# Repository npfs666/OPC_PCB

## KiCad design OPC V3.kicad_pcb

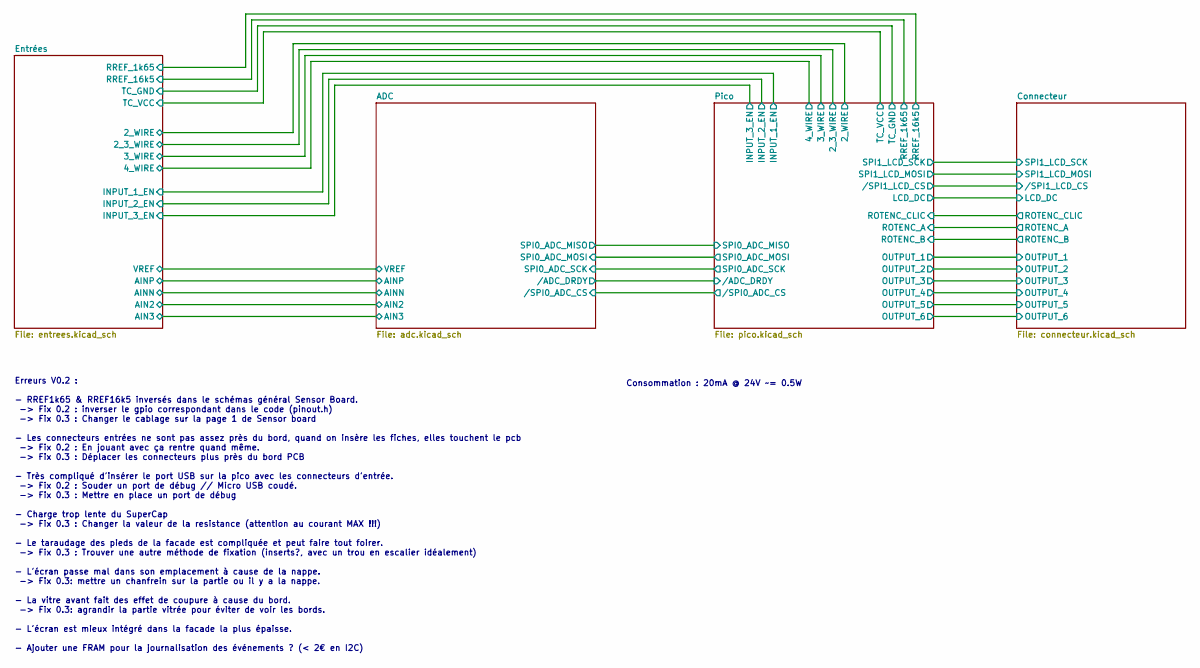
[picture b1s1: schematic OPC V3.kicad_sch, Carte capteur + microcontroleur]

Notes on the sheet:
Erreurs V0.2 : - RREF1k65 & RREF16k5 inversés dans le schémas général Sensor Board. -> Fix 0.2 : inverser le gpio correspondant dans le code (pinout.h) -> Fix 0.3 : Changer le cablage sur la page 1 de Sensor board - Les connecteurs entrées ne sont pas assez près du bord, quand on insère les fiches,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
Consommation : 20mA @ 24V ~= 0.5W

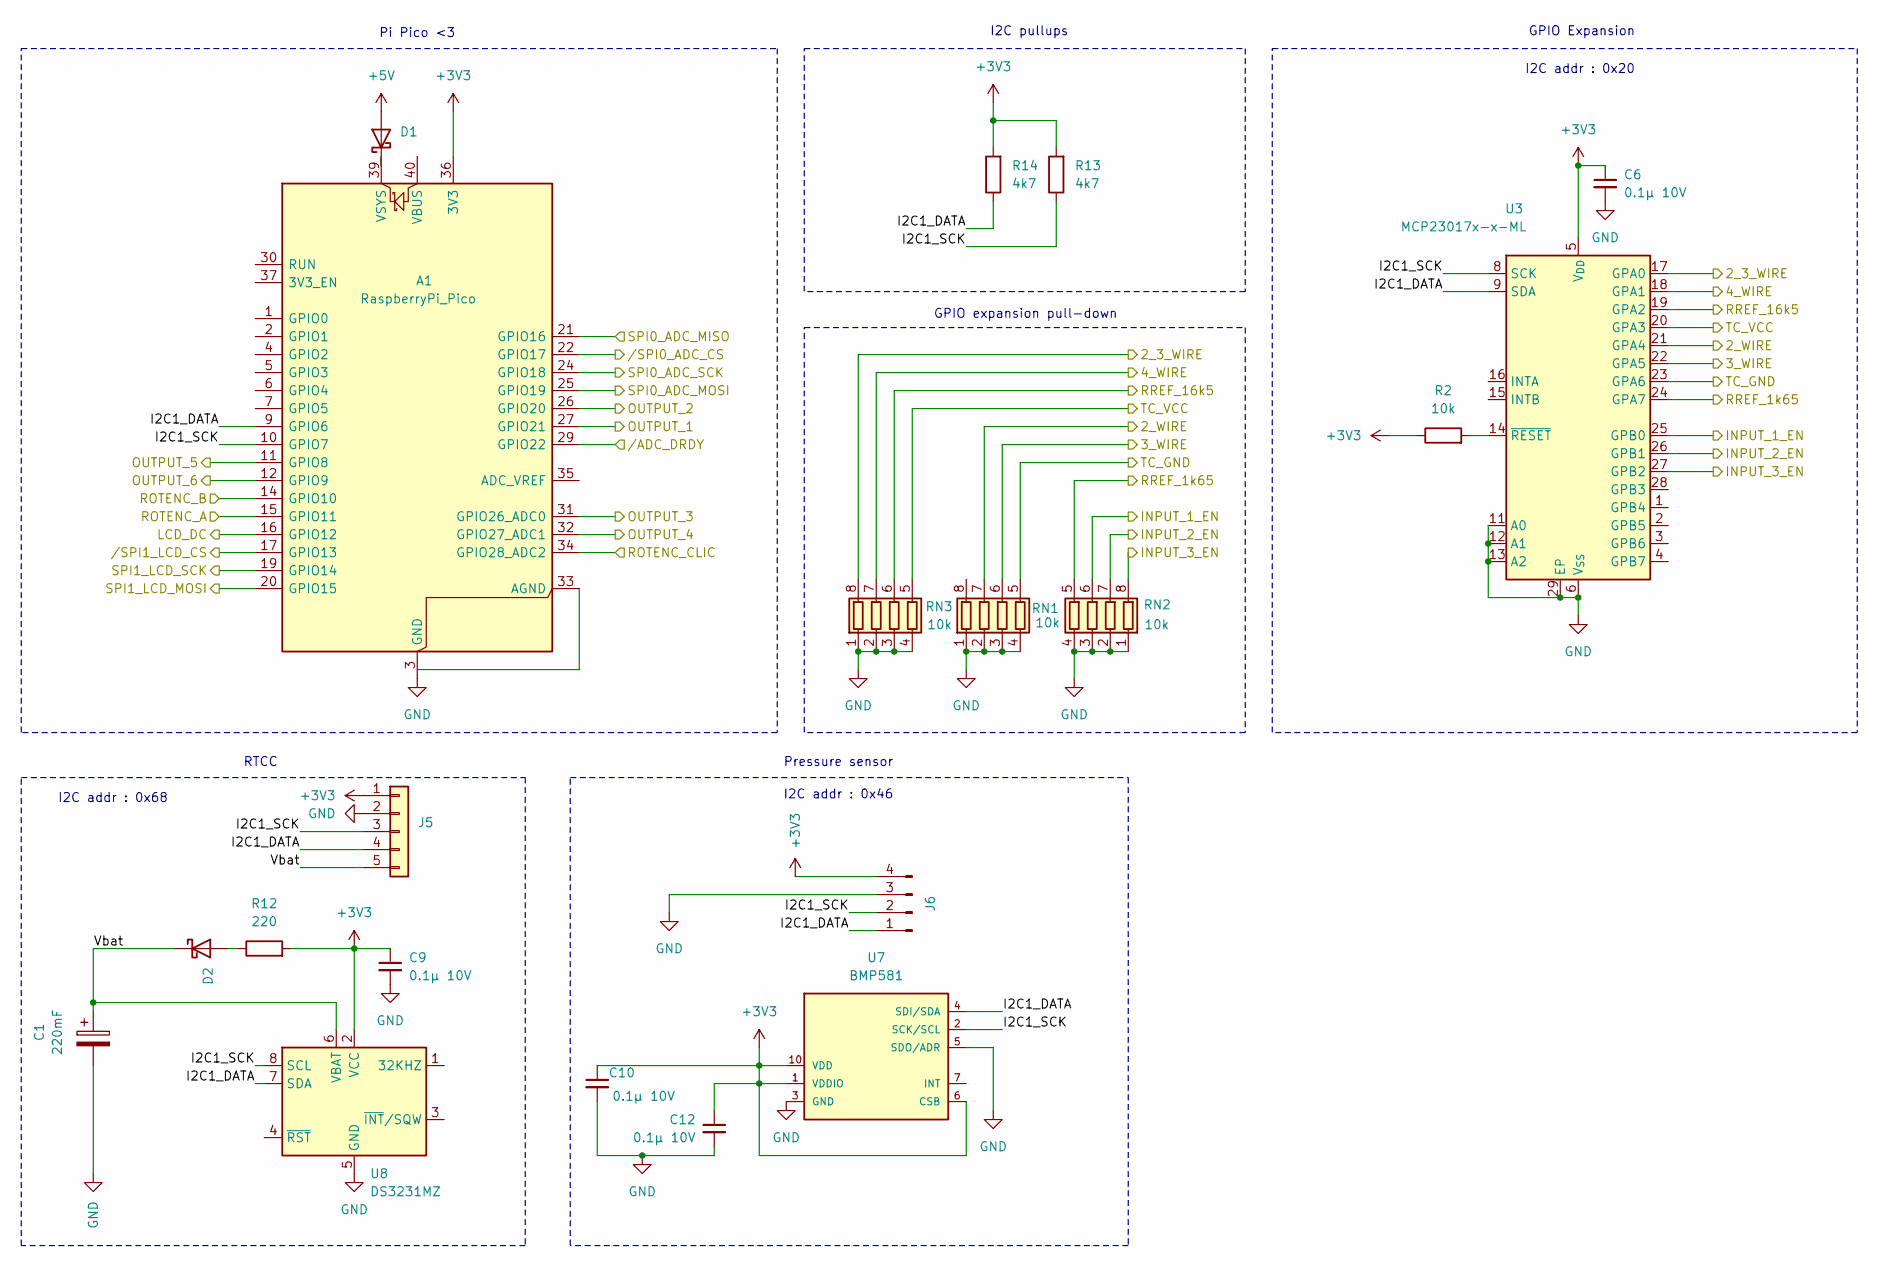
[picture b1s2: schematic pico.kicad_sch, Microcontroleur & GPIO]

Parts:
A1: RaspberryPi_Pico; RaspberryPi_Pico_Common_THT_SIMPLE; MPN SC1631
C1: 220mF; CP_Radial_D13.0mm_P5.00mm; MPN 3-158-695
C6, C9, C12: 0.1µ 10V; C_0603_1608Metric_Pad1.08x0.95mm_HandSolder; MPN 885012206020; LCSC Part # C14663
C10: 0.1µ 10V; C_0603_1608Metric; MPN 885012206020; LCSC Part # C14663
D1, D2: D_Schottky; D_SMA; MPN B140-E3/61T; LCSC Part # C14996
J5: Conn_01x05; PinHeader_1x05_P2.54mm_Vertical
J6: Conn_01x04_Pin; PinHeader_1x04_P2.54mm_Vertical
R2: 10k; R_0603_1608Metric_Pad0.98x0.95mm_HandSolder; MPN ERJ-3EKF1002V; LCSC Part # C25804
R12: 220; R_0603_1608Metric_Pad0.98x0.95mm_HandSolder; MPN ERJ-3GEYJ221V; LCSC Part # C22962
R13, R14: 4k7; R_0603_1608Metric_Pad0.98x0.95mm_HandSolder; MPN ERJ-3GEYJ472V; LCSC Part # C23162
RN1, RN2, RN3: 10k; R_Array_Concave_4x0603; MPN WA06X103JTL; LCSC Part # C29718
U3: MCP23017x-x-ML; QFN-28-1EP_6x6mm_P0.65mm_EP4.25x4.25mm; MPN MCP23017-E/ML; LCSC Part # C629439
U7: BMP581; MPN BMP581
U8: DS3231MZ; SOIC-8_3.9x4.9mm_P1.27mm; MPN DS3231MZ+TRL; LCSC Part # C107410

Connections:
+3V3: A1.36 (3V3), C6.1, C9.1, C10.1, C12.1, J5.1, J6.4, R2.1, R12.2, R13.2, R14.2, U3.5 (V_{DD}), U7.1 (VDDIO), U7.6 (CSB), U7.10 (VDD), U8.2 (VCC); also elsewhere on the board
+5V: D1.2 (A); also elsewhere on the board
/ADC/SPI0_ADC_MISO: A1.21 (GPIO16); also elsewhere on the board
/ADC/SPI0_ADC_MOSI: A1.25 (GPIO19); also elsewhere on the board
/ADC/SPI0_ADC_SCK: A1.24 (GPIO18); also elsewhere on the board
/ADC//ADC_DRDY: A1.29 (GPIO22); also elsewhere on the board
/ADC//SPI0_ADC_CS: A1.22 (GPIO17); also elsewhere on the board
/Connecteur/LCD_DC: A1.16 (GPIO12); also elsewhere on the board
/Connecteur/OUTPUT_1: A1.27 (GPIO21); also elsewhere on the board
/Connecteur/OUTPUT_2: A1.26 (GPIO20); also elsewhere on the board
/Connecteur/OUTPUT_3: A1.31 (GPIO26_ADC0); also elsewhere on the board
/Connecteur/OUTPUT_4: A1.32 (GPIO27_ADC1); also elsewhere on the board
/Connecteur/OUTPUT_5: A1.11 (GPIO8); also elsewhere on the board
/Connecteur/OUTPUT_6: A1.12 (GPIO9); also elsewhere on the board
/Connecteur/ROTENC_A: A1.15 (GPIO11); also elsewhere on the board
/Connecteur/ROTENC_B: A1.14 (GPIO10); also elsewhere on the board
/Connecteur/ROTENC_CLIC: A1.34 (GPIO28_ADC2); also elsewhere on the board
/Connecteur/SPI1_LCD_MOSI: A1.20 (GPIO15); also elsewhere on the board
/Connecteur/SPI1_LCD_SCK: A1.19 (GPIO14); also elsewhere on the board
/Connecteur//SPI1_LCD_CS: A1.17 (GPIO13); also elsewhere on the board
/Entrées/2_3_WIRE: RN3.8 (R1.2), U3.17 (GPA0); also elsewhere on the board
/Entrées/2_WIRE: RN1.7 (R2.2), U3.21 (GPA4); also elsewhere on the board
/Entrées/3_WIRE: RN1.6 (R3.2), U3.22 (GPA5); also elsewhere on the board
/Entrées/4_WIRE: RN3.7 (R2.2), U3.18 (GPA1); also elsewhere on the board
/Entrées/INPUT_1_EN: RN2.6 (R3.2), U3.25 (GPB0); also elsewhere on the board
/Entrées/INPUT_2_EN: RN2.7 (R2.2), U3.26 (GPB1); also elsewhere on the board
/Entrées/INPUT_3_EN: RN2.8 (R1.2), U3.27 (GPB2); also elsewhere on the board
/Entrées/RREF_1k65: RN3.6 (R3.2), U3.19 (GPA2); also elsewhere on the board
/Entrées/RREF_16k5: RN2.5 (R4.2), U3.24 (GPA7); also elsewhere on the board
/Entrées/TC_GND: RN1.5 (R4.2), U3.23 (GPA6); also elsewhere on the board
/Entrées/TC_VCC: RN3.5 (R4.2), U3.20 (GPA3); also elsewhere on the board
/Pico/I2C1_DATA: A1.9 (GPIO6), J5.4, J6.1, R14.1, U3.9 (SDA), U7.4 (SDI/SDA), U8.7 (SDA)
/Pico/I2C1_SCK: A1.10 (GPIO7), J5.3, J6.2, R13.1, U3.8 (SCK), U7.2 (SCK/SCL), U8.8 (SCL)
/Pico/Vbat: C1.1, D2.1 (K), J5.5, U8.6 (VBAT)
GND: A1.3 (GND), A1.8 (GND), A1.13 (GND), A1.18 (GND), A1.23 (GND), A1.28 (GND), A1.38 (GND), C1.2, C6.2, C9.2, C10.2, C12.2, J5.2, J6.3, RN1.1 (R1.1), RN1.2 (R2.1), RN1.3 (R3.1), RN1.4 (R4.1), RN2.1 (R1.1), RN2.2 (R2.1), RN2.3 (R3.1), RN2.4 (R4.1), RN3.1 (R1.1), RN3.2 (R2.1), RN3.3 (R3.1), RN3.4 (R4.1), U3.6 (V_{SS}), U3.11 (A0), U3.12 (A1), U3.13 (A2), U3.29 (EP), U7.3 (GND), U7.5 (SDO/ADR), U7.8 (GND), U7.9 (GND), U8.5 (GND); also elsewhere on the board
unnamed: A1.39 (VSYS), D1.1 (K)
unnamed: D2.2 (A), R12.1
unnamed: R2.2, U3.14 (~RESET)

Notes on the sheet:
I2C pullups
Pressure sensor
I2C addr : 0x46
I2C addr : 0x68
I2C addr : 0x20
GPIO Expansion
GPIO expansion pull-down
Pi Pico <3
RTCC

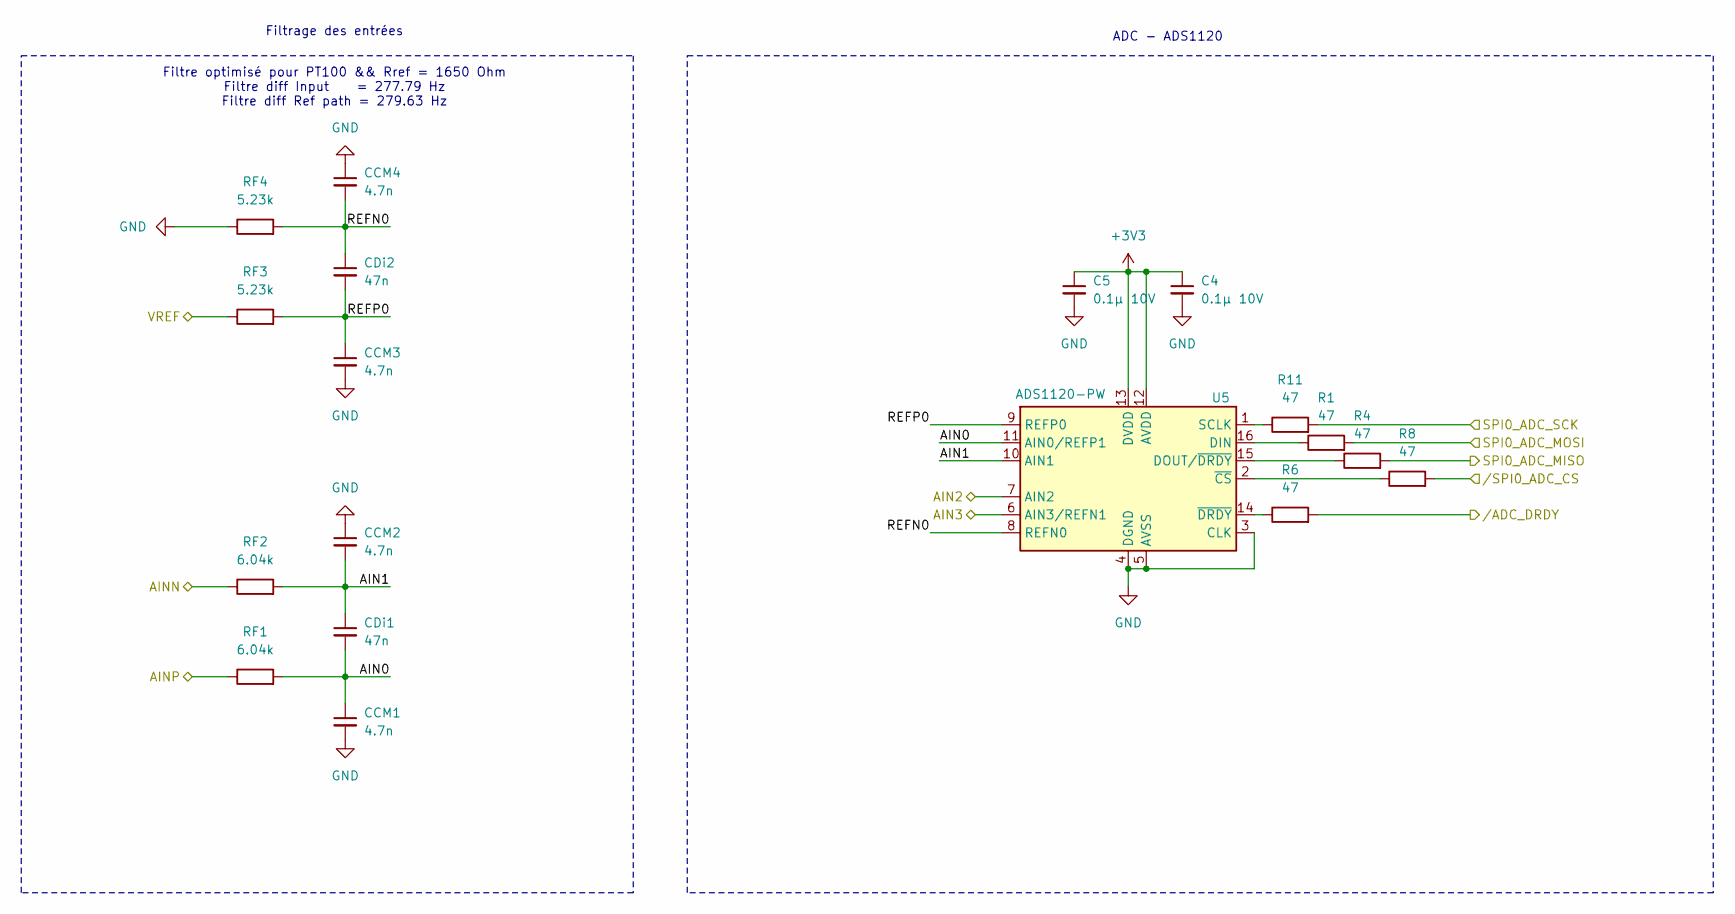
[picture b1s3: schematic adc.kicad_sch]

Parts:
C4, C5: 0.1µ 10V; C_0603_1608Metric_Pad1.08x0.95mm_HandSolder; MPN 885012206020; LCSC Part # C14663
CCM1, CCM2, CCM3, CCM4: 4.7n; C_0805_2012Metric_Pad1.18x1.45mm_HandSolder; MPN GCM1885C1H472JA16J; LCSC Part # C77063
CDi1, CDi2: 47n; C_1206_3216Metric_Pad1.33x1.80mm_HandSolder; MPN GRM3195C1H473JA05D; LCSC Part # C21812
R1, R4, R6, R8, R11: 47; R_0603_1608Metric_Pad0.98x0.95mm_HandSolder; MPN ERJ-3GEYJ470V; LCSC Part # C23182
RF1, RF2: 6.04k; R_0603_1608Metric_Pad0.98x0.95mm_HandSolder; MPN ERA-3AED6041V; LCSC Part # C403295
RF3, RF4: 5.23k; R_0603_1608Metric_Pad0.98x0.95mm_HandSolder; MPN ERA-3AEB5231V; LCSC Part # C4165570
U5: ADS1120-PW; TSSOP-16_4.4x5mm_P0.65mm; MPN ADS1120IPWR; LCSC Part # C84284

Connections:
+3V3: C4.1, C5.1, U5.12 (AVDD), U5.13 (DVDD); also elsewhere on the board
/ADC/AIN0: CCM1.1, CDi1.2, RF1.2, U5.11 (AIN0/REFP1)
/ADC/AIN1: CCM2.2, CDi1.1, RF2.2, U5.10 (AIN1)
/ADC/AIN2: U5.7 (AIN2); also elsewhere on the board
/ADC/AIN3: U5.6 (AIN3/REFN1); also elsewhere on the board
/ADC/AINN: RF2.1; also elsewhere on the board
/ADC/AINP: RF1.1; also elsewhere on the board
/ADC/REFN0: CCM4.2, CDi2.1, RF4.2, U5.8 (REFN0)
/ADC/REFP0: CCM3.1, CDi2.2, RF3.2, U5.9 (REFP0)
/ADC/SPI0_ADC_MISO: R4.2; also elsewhere on the board
/ADC/SPI0_ADC_MOSI: R1.2; also elsewhere on the board
/ADC/SPI0_ADC_SCK: R11.2; also elsewhere on the board
/ADC/VREF: RF3.1; also elsewhere on the board
/ADC//ADC_DRDY: R6.2; also elsewhere on the board
/ADC//SPI0_ADC_CS: R8.2; also elsewhere on the board
GND: C4.2, C5.2, CCM1.2, CCM2.1, CCM3.2, CCM4.1, RF4.1, U5.3 (CLK), U5.4 (DGND), U5.5 (AVSS); also elsewhere on the board
unnamed: R1.1, U5.16 (DIN)
unnamed: R4.1, U5.15 (DOUT/~DRDY)
unnamed: R11.1, U5.1 (SCLK)
unnamed: R8.1, U5.2 (~CS)
unnamed: R6.1, U5.14 (~DRDY)

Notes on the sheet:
Filtrage des entrées
Filtre optimisé pour PT100 && Rref = 1650 Ohm Filtre diff Input = 277.79 Hz Filtre diff Ref path = 279.63 Hz
ADC - ADS1120

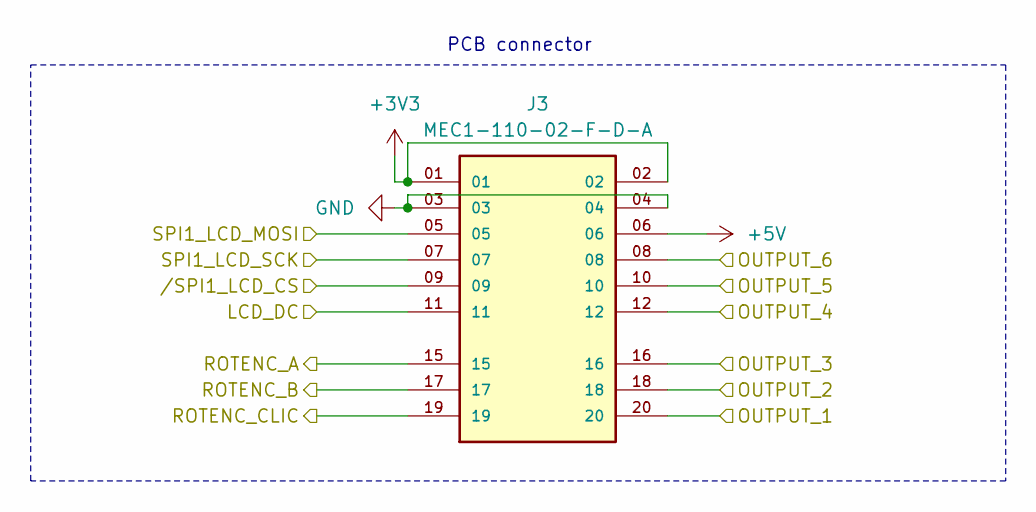
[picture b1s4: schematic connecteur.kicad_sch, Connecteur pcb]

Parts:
J3: MEC1-110-02-F-D-A; MEC1-110-02-F-D-A-MALE

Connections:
+3V3: J3.01, J3.02; also elsewhere on the board
+5V: J3.06; also elsewhere on the board
/Connecteur/LCD_DC: J3.11; also elsewhere on the board
/Connecteur/OUTPUT_1: J3.20; also elsewhere on the board
/Connecteur/OUTPUT_2: J3.18; also elsewhere on the board
/Connecteur/OUTPUT_3: J3.16; also elsewhere on the board
/Connecteur/OUTPUT_4: J3.12; also elsewhere on the board
/Connecteur/OUTPUT_5: J3.10; also elsewhere on the board
/Connecteur/OUTPUT_6: J3.08; also elsewhere on the board
/Connecteur/ROTENC_A: J3.15; also elsewhere on the board
/Connecteur/ROTENC_B: J3.17; also elsewhere on the board
/Connecteur/ROTENC_CLIC: J3.19; also elsewhere on the board
/Connecteur/SPI1_LCD_MOSI: J3.05; also elsewhere on the board
/Connecteur/SPI1_LCD_SCK: J3.07; also elsewhere on the board
/Connecteur//SPI1_LCD_CS: J3.09; also elsewhere on the board
GND: J3.03, J3.04; also elsewhere on the board

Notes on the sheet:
PCB connector

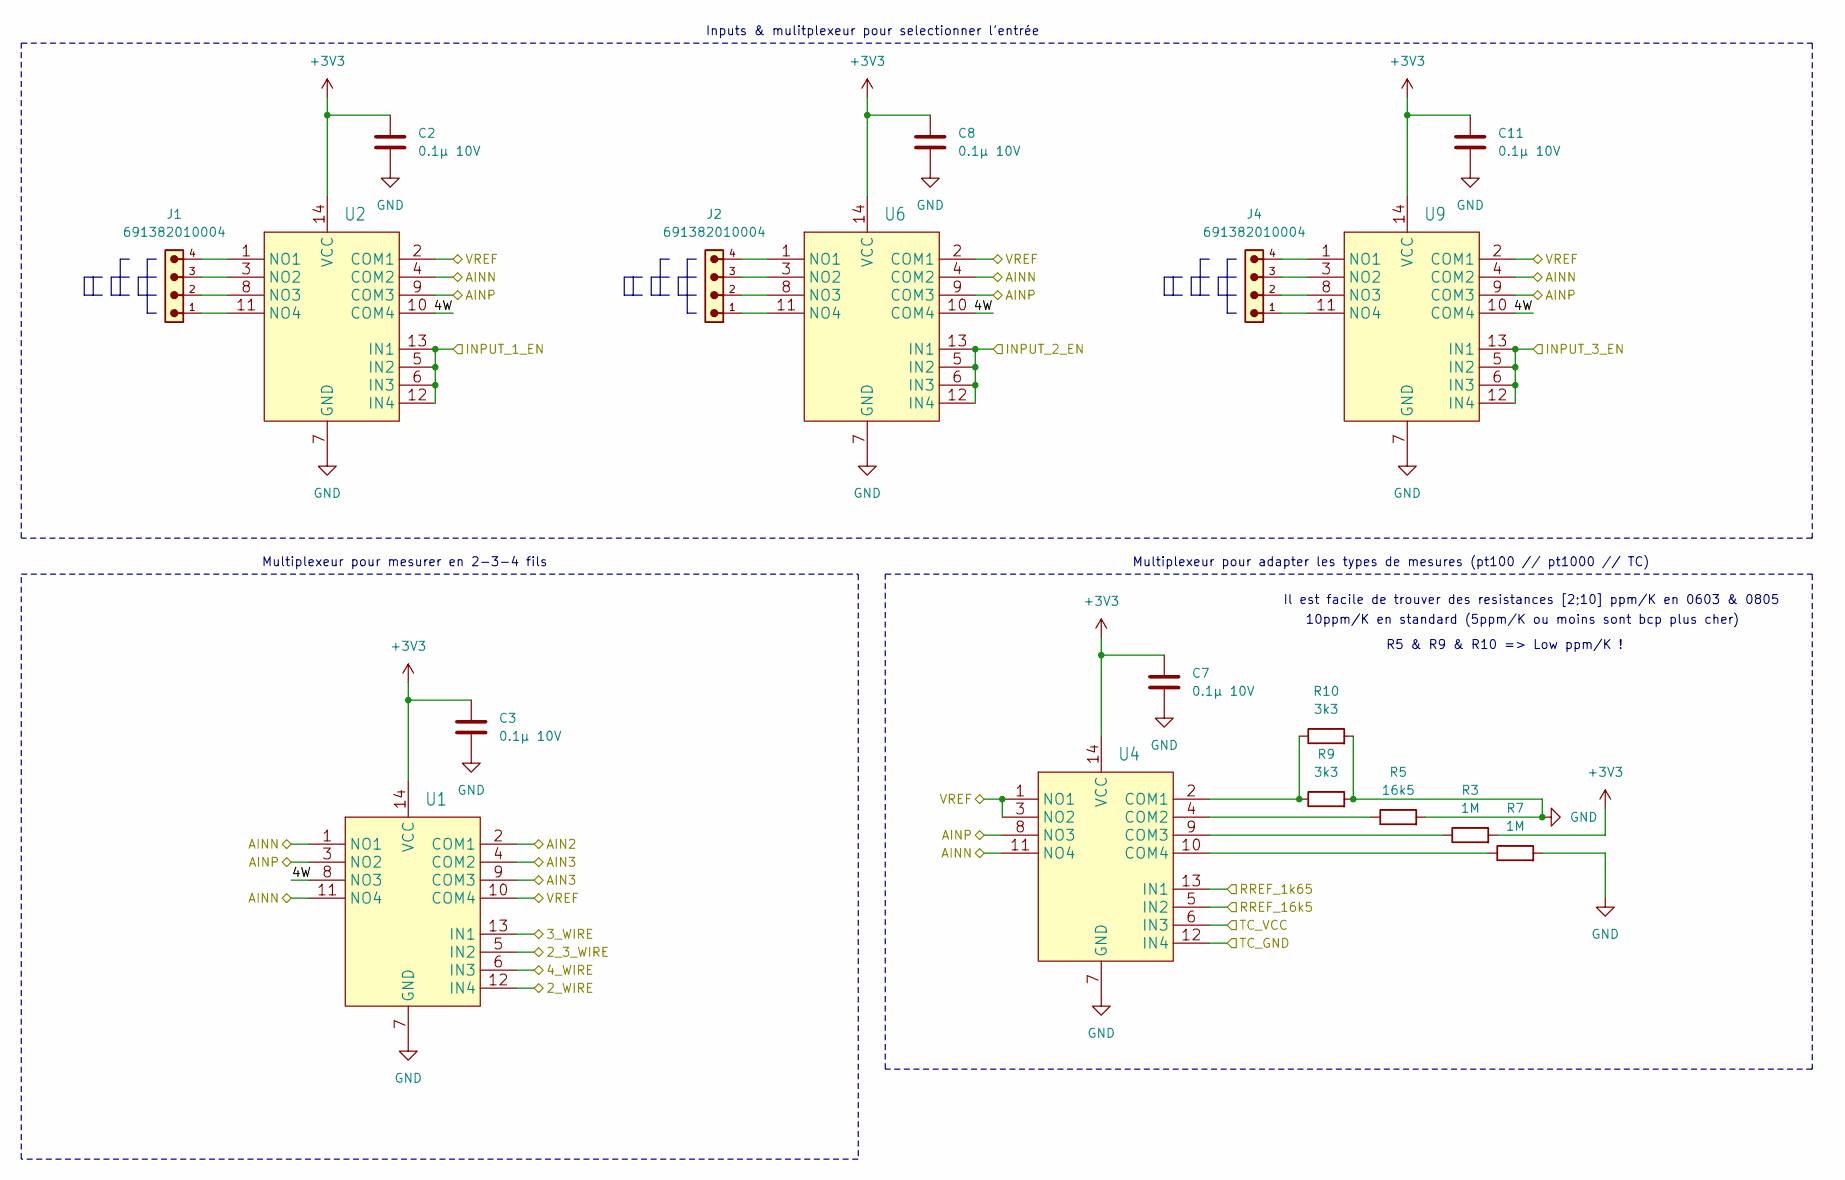
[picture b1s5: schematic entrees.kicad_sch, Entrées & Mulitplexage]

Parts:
C2, C3, C7, C8, C11: 0.1µ 10V; C_0603_1608Metric_Pad1.08x0.95mm_HandSolder; MPN 885012206020; LCSC Part # C14663
J1, J2, J4: 691382010004; MPN 691382010004
R3, R7: 1M; R_0805_2012Metric; MPN ERJ-3EKF1004V; LCSC Part # C17514
R5: 16k5; R_0805_2012Metric; MPN ERA-6ARB1652V; LCSC Part # C47115532
R9, R10: 3k3; R_0805_2012Metric; MPN ERA-6ARB332V; LCSC Part # C19679588
U1, U2, U4, U6, U9: TS3A4751PWR; TSSOP-14_4.4x5mm_P0.65mm; MPN TS3A4751PWR; LCSC Part # TS3A4751PWR

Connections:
+3V3: C2.1, C3.1, C7.1, C8.1, C11.1, R3.2, U1.14 (VCC), U2.14 (VCC), U4.14 (VCC), U6.14 (VCC), U9.14 (VCC); also elsewhere on the board
/ADC/AIN2: U1.2 (COM1); also elsewhere on the board
/ADC/AIN3: U1.4 (COM2), U1.9 (COM3); also elsewhere on the board
/ADC/AINN: U1.1 (NO1), U1.11 (NO4), U2.4 (COM2), U4.11 (NO4), U6.4 (COM2), U9.4 (COM2); also elsewhere on the board
/ADC/AINP: U1.3 (NO2), U2.9 (COM3), U4.8 (NO3), U6.9 (COM3), U9.9 (COM3); also elsewhere on the board
/ADC/VREF: U1.10 (COM4), U2.2 (COM1), U4.1 (NO1), U4.3 (NO2), U6.2 (COM1), U9.2 (COM1); also elsewhere on the board
/Entrées/2_3_WIRE: U1.5 (IN2); also elsewhere on the board
/Entrées/2_WIRE: U1.12 (IN4); also elsewhere on the board
/Entrées/3_WIRE: U1.13 (IN1); also elsewhere on the board
/Entrées/4W: U1.8 (NO3), U2.10 (COM4), U6.10 (COM4), U9.10 (COM4)
/Entrées/4_WIRE: U1.6 (IN3); also elsewhere on the board
/Entrées/INPUT_1_EN: U2.5 (IN2), U2.6 (IN3), U2.12 (IN4), U2.13 (IN1); also elsewhere on the board
/Entrées/INPUT_2_EN: U6.5 (IN2), U6.6 (IN3), U6.12 (IN4), U6.13 (IN1); also elsewhere on the board
/Entrées/INPUT_3_EN: U9.5 (IN2), U9.6 (IN3), U9.12 (IN4), U9.13 (IN1); also elsewhere on the board
/Entrées/RREF_1k65: U4.13 (IN1); also elsewhere on the board
/Entrées/RREF_16k5: U4.5 (IN2); also elsewhere on the board
/Entrées/TC_GND: U4.12 (IN4); also elsewhere on the board
/Entrées/TC_VCC: U4.6 (IN3); also elsewhere on the board
GND: C2.2, C3.2, C7.2, C8.2, C11.2, R5.2, R7.2, R9.2, R10.2, U1.7 (GND), U2.7 (GND), U4.7 (GND), U6.7 (GND), U9.7 (GND); also elsewhere on the board
unnamed: J1.4, U2.1 (NO1)
unnamed: J1.3, U2.3 (NO2)
unnamed: J1.2, U2.8 (NO3)
unnamed: J1.1, U2.11 (NO4)
unnamed: R9.1, R10.1, U4.2 (COM1)
unnamed: R5.1, U4.4 (COM2)
unnamed: R3.1, U4.9 (COM3)
unnamed: R7.1, U4.10 (COM4)
unnamed: J2.4, U6.1 (NO1)
unnamed: J2.3, U6.3 (NO2)
unnamed: J2.2, U6.8 (NO3)
unnamed: J2.1, U6.11 (NO4)
unnamed: J4.4, U9.1 (NO1)
unnamed: J4.3, U9.3 (NO2)
unnamed: J4.2, U9.8 (NO3)
unnamed: J4.1, U9.11 (NO4)

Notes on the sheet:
R5 & R9 & R10 => Low ppm/K !
Multiplexeur pour adapter les types de mesures (pt100 // pt1000 // TC)
10ppm/K en standard (5ppm/K ou moins sont bcp plus cher)
Il est facile de trouver des resistances [2;10] ppm/K en 0603 & 0805
Multiplexeur pour mesurer en 2-3-4 fils
Inputs & mulitplexeur pour selectionner l'entrée

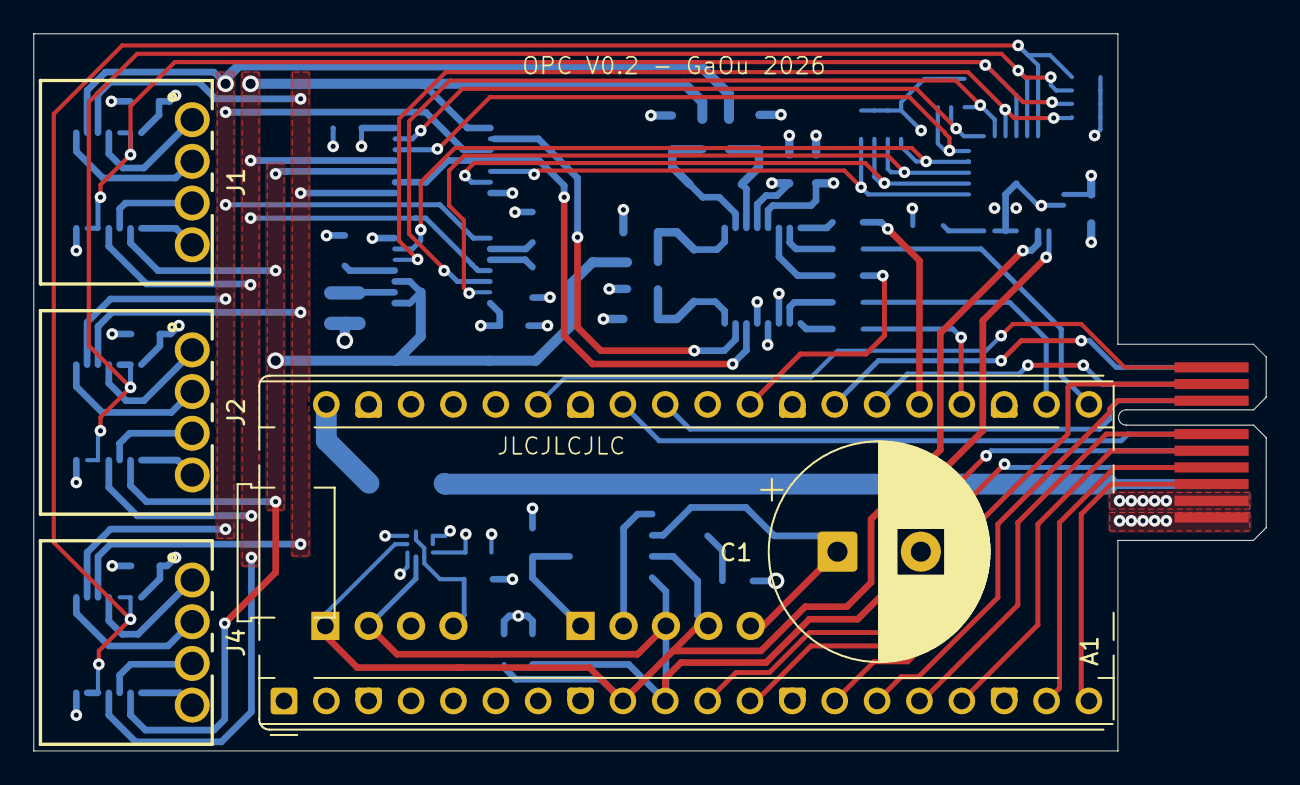
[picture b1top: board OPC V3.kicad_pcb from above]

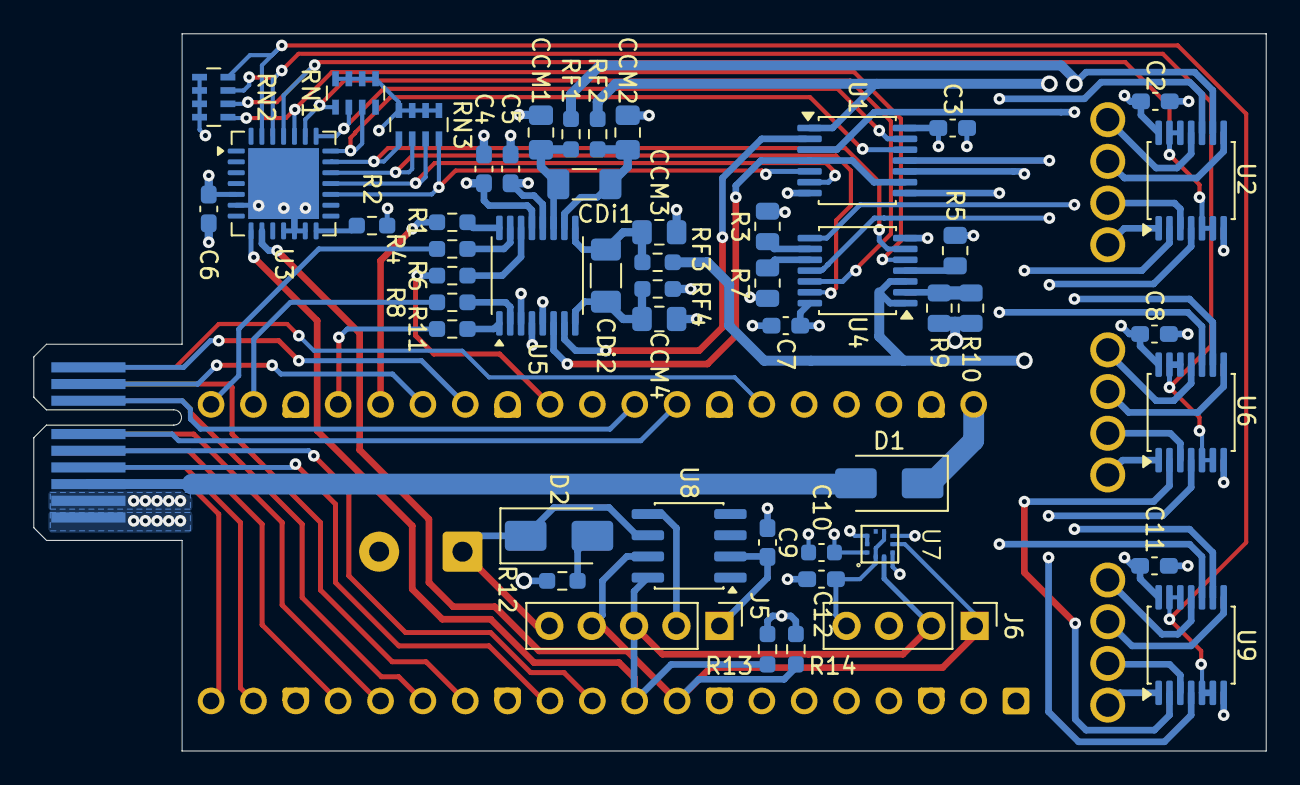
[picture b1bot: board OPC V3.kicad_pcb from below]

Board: 4 copper layers, 73.9 x 43.0 mm, 57 parts (51 on the bottom side), 69 nets.

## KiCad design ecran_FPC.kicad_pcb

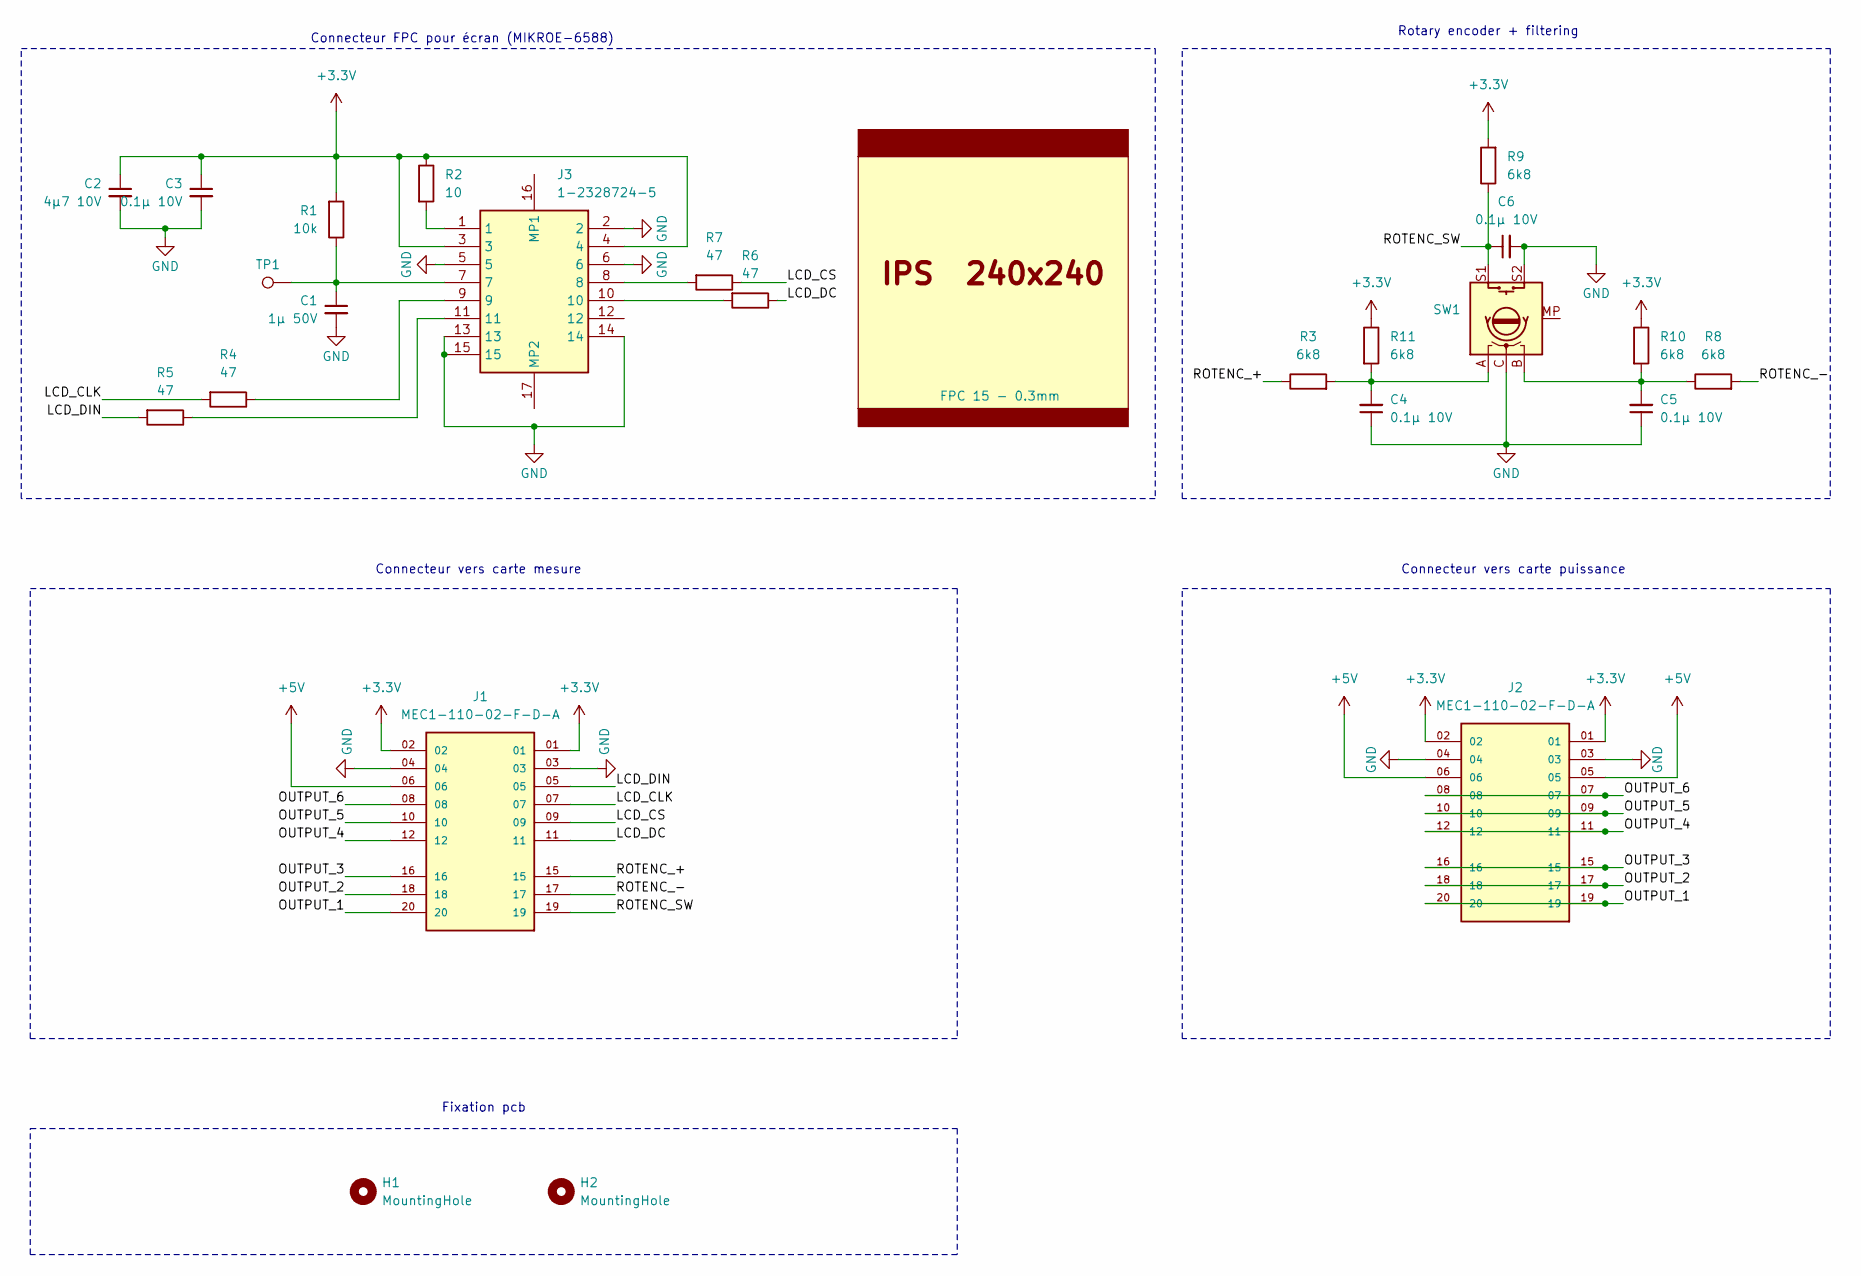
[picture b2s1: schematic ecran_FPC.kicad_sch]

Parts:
C1: 1µ 50V; C_0805_2012Metric_Pad1.18x1.45mm_HandSolder; MPN GRM219R61H105MA73D; LCSC Part # C28323
C2: 4µ7 10V; C_0805_2012Metric_Pad1.18x1.45mm_HandSolder; MPN GRM21BR71A475KE51K; LCSC Part # C1779
C3, C4, C5, C6: 0.1µ 10V; C_0603_1608Metric_Pad1.08x0.95mm_HandSolder; MPN 885012206020; LCSC Part # C14663
H1, H2: MountingHole; MountingHole_3.2mm_M3_DIN965
J1, J2: MEC1-110-02-F-D-A; SAMTEC_MEC1-110-02-F-D-A; MPN MEC1-110-02-F-D-A
J3: 1-2328724-5; 123287245; Mouser Part Number 571-1-2328724-5
R1: 10k; R_0603_1608Metric_Pad0.98x0.95mm_HandSolder; MPN ERJ-3EKF1002V; LCSC Part # C25804
R2: 10; R_1206_3216Metric_Pad1.30x1.75mm; MPN ERJ-U08J100V; LCSC Part # C17903
R3, R8, R9, R10, R11: 6k8; R_0603_1608Metric_Pad0.98x0.95mm_HandSolder; MPN ERJ-3EKF6801V; LCSC Part # C23212
R4, R5, R6, R7: 47; R_0603_1608Metric_Pad0.98x0.95mm_HandSolder; MPN ERJ-3GEYJ470V; LCSC Part # C23182
SW1: PEC11L-4220F-S0015; PEC11L4220KS0015; MPN PEC11L-4220F-S0015
TP1: TestPoint; TestPoint_Pad_1.5x1.5mm
U2: IPS_240x240; FPC 15 - 0.3mm; MPN MIKROE-6588

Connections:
+3.3V: C2.1, C3.1, J1.01, J1.02, J2.01, J2.02, J3.3, J3.4, R1.2, R2.1, R9.2, R10.1, R11.1
+5V: J1.06, J2.05, J2.06
/LCD_CLK: J1.07, R4.2
/LCD_CS: J1.09, R7.1
/LCD_DC: J1.11, R6.1
/LCD_DIN: J1.05, R5.2
/OUTPUT_1: J1.20, J2.19, J2.20
/OUTPUT_2: J1.18, J2.17, J2.18
/OUTPUT_3: J1.16, J2.15, J2.16
/OUTPUT_4: J1.12, J2.11, J2.12
/OUTPUT_5: J1.10, J2.09, J2.10
/OUTPUT_6: J1.08, J2.07, J2.08
/ROTENC_+: J1.15, R3.1
/ROTENC_-: J1.17, R8.2
/ROTENC_SW: C6.1, J1.19, R9.1, SW1.S1
GND: C1.2, C2.2, C3.2, C4.1, C5.1, C6.2, J1.03, J1.04, J2.03, J2.04, J3.2, J3.5, J3.6, J3.13, J3.14, J3.15, SW1.C, SW1.S2
unnamed: C1.1, J3.7, R1.1, TP1.1 (1_1)
unnamed: C4.2, R3.2, R11.2, SW1.A
unnamed: C5.2, R8.1, R10.2, SW1.B
unnamed: J3.1, R2.2
unnamed: J3.8, R7.2
unnamed: J3.9, R4.1
unnamed: J3.10, R6.2
unnamed: J3.11, R5.1

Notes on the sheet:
Connecteur FPC pour écran (MIKROE-6588)
Connecteur vers carte mesure
Connecteur vers carte puissance
Rotary encoder + filtering
Fixation pcb

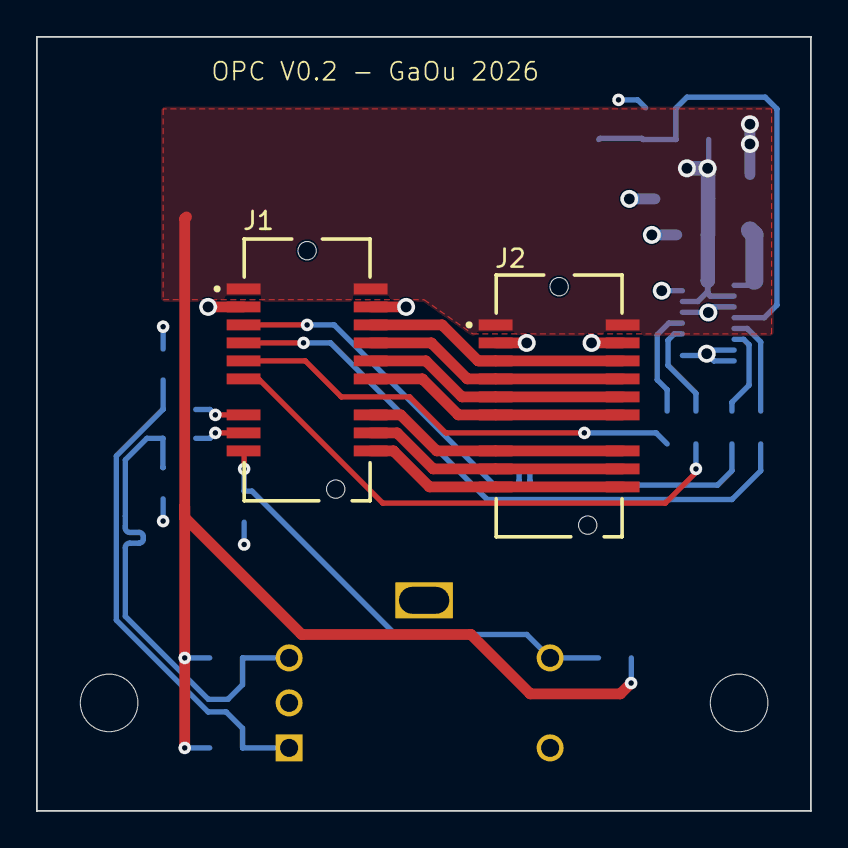
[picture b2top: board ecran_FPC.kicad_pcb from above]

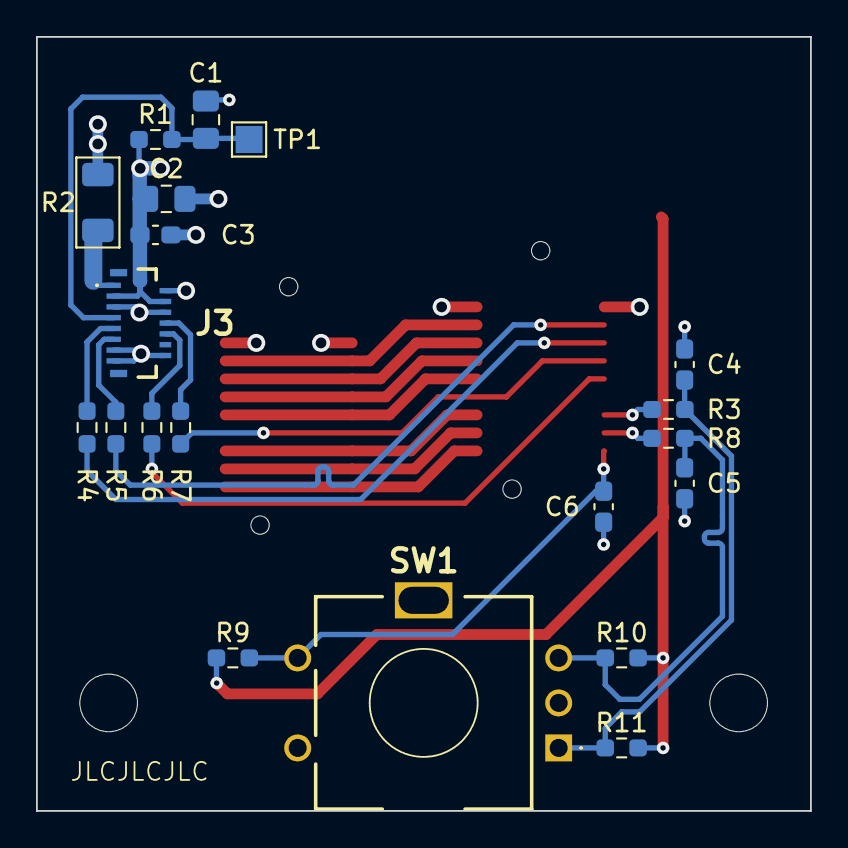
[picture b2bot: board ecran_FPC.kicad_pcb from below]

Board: 4 copper layers, 43.0 x 43.0 mm, 24 parts (20 on the bottom side), 24 nets.
